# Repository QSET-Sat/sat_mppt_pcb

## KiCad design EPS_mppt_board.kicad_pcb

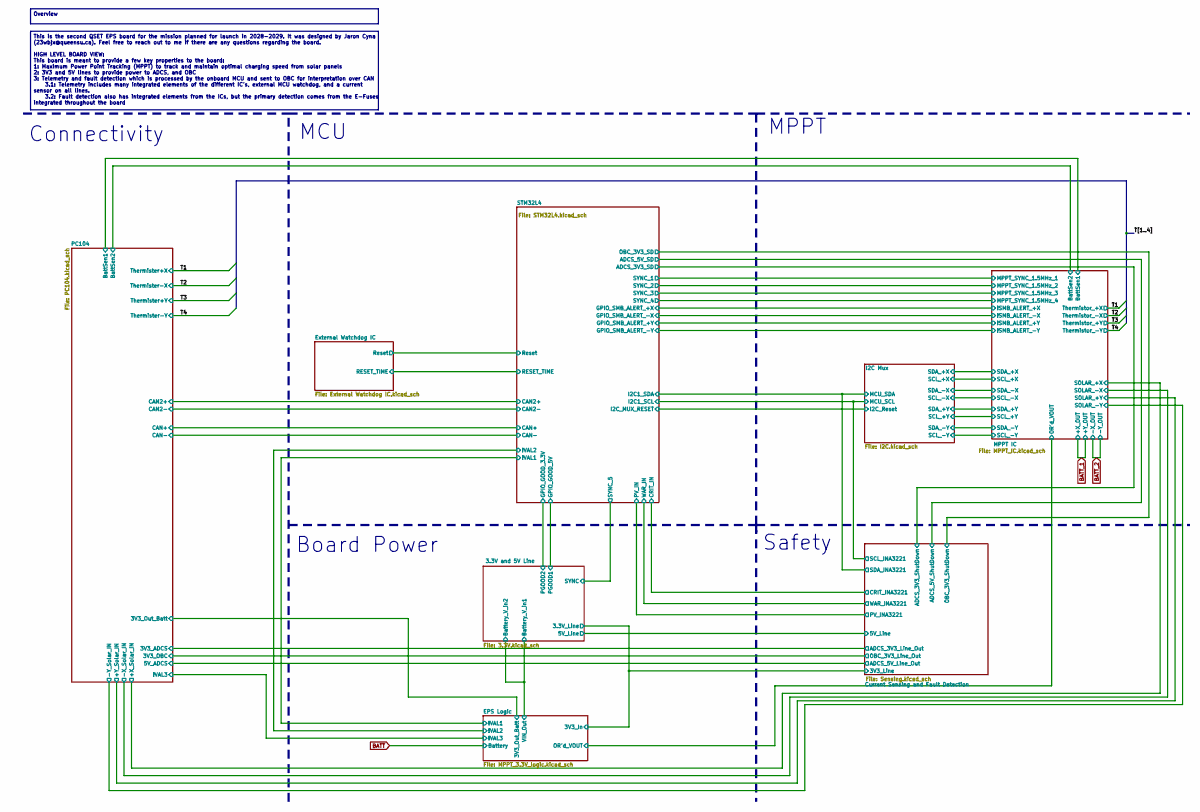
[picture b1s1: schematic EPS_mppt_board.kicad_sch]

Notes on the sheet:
MCU
MPPT
Safety
Board Power
Connectivity
This is the second QSET EPS board for the mission planned for launch in 2028-2029. It was designed by Jaron Cyna (23wbjx@queensu.ca). Feel free to reach out to me if there are any questions regarding the board. HIGH LEVEL BOARD VIEW: This board is meant to provide a few key properties to the board: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
Overview

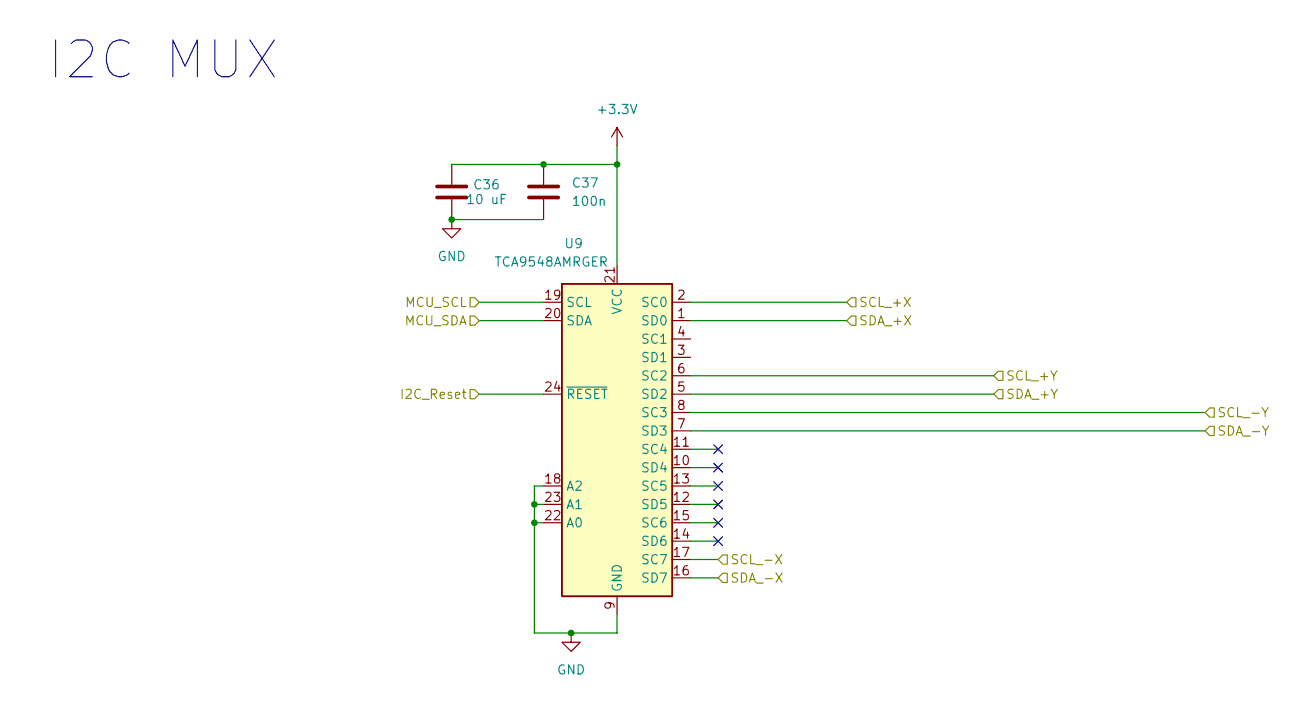
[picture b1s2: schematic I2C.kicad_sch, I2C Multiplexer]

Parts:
C36: 10 uF; C_0603_1608Metric
C37: 100n; C_0603_1608Metric; MANUFACTURER_PART_NUMBER C0603X104K5RACTU
U9: TCA9548AMRGER; Texas_RGE0024C_VQFN-24-1EP_4x4mm_P0.5mm_EP2.1x2.1mm

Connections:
+3.3V: C36.2, C37.1, U9.21 (VCC); also elsewhere on the board
/Current Sensing and Fault Detection/SCL_INA3221: U9.19 (SCL); also elsewhere on the board
/Current Sensing and Fault Detection/SDA_INA3221: U9.20 (SDA); also elsewhere on the board
/I2C Mux/I2C_Reset: U9.24 (~RESET); also elsewhere on the board
/I2C Mux/SCL_+X: U9.2 (SC0); also elsewhere on the board
/I2C Mux/SCL_+Y: U9.6 (SC2); also elsewhere on the board
/I2C Mux/SCL_-X: U9.17 (SC7); also elsewhere on the board
/I2C Mux/SCL_-Y: U9.8 (SC3); also elsewhere on the board
/I2C Mux/SDA_+X: U9.1 (SD0); also elsewhere on the board
/I2C Mux/SDA_+Y: U9.5 (SD2); also elsewhere on the board
/I2C Mux/SDA_-X: U9.16 (SD7); also elsewhere on the board
/I2C Mux/SDA_-Y: U9.7 (SD3); also elsewhere on the board

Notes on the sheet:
I2C MUX

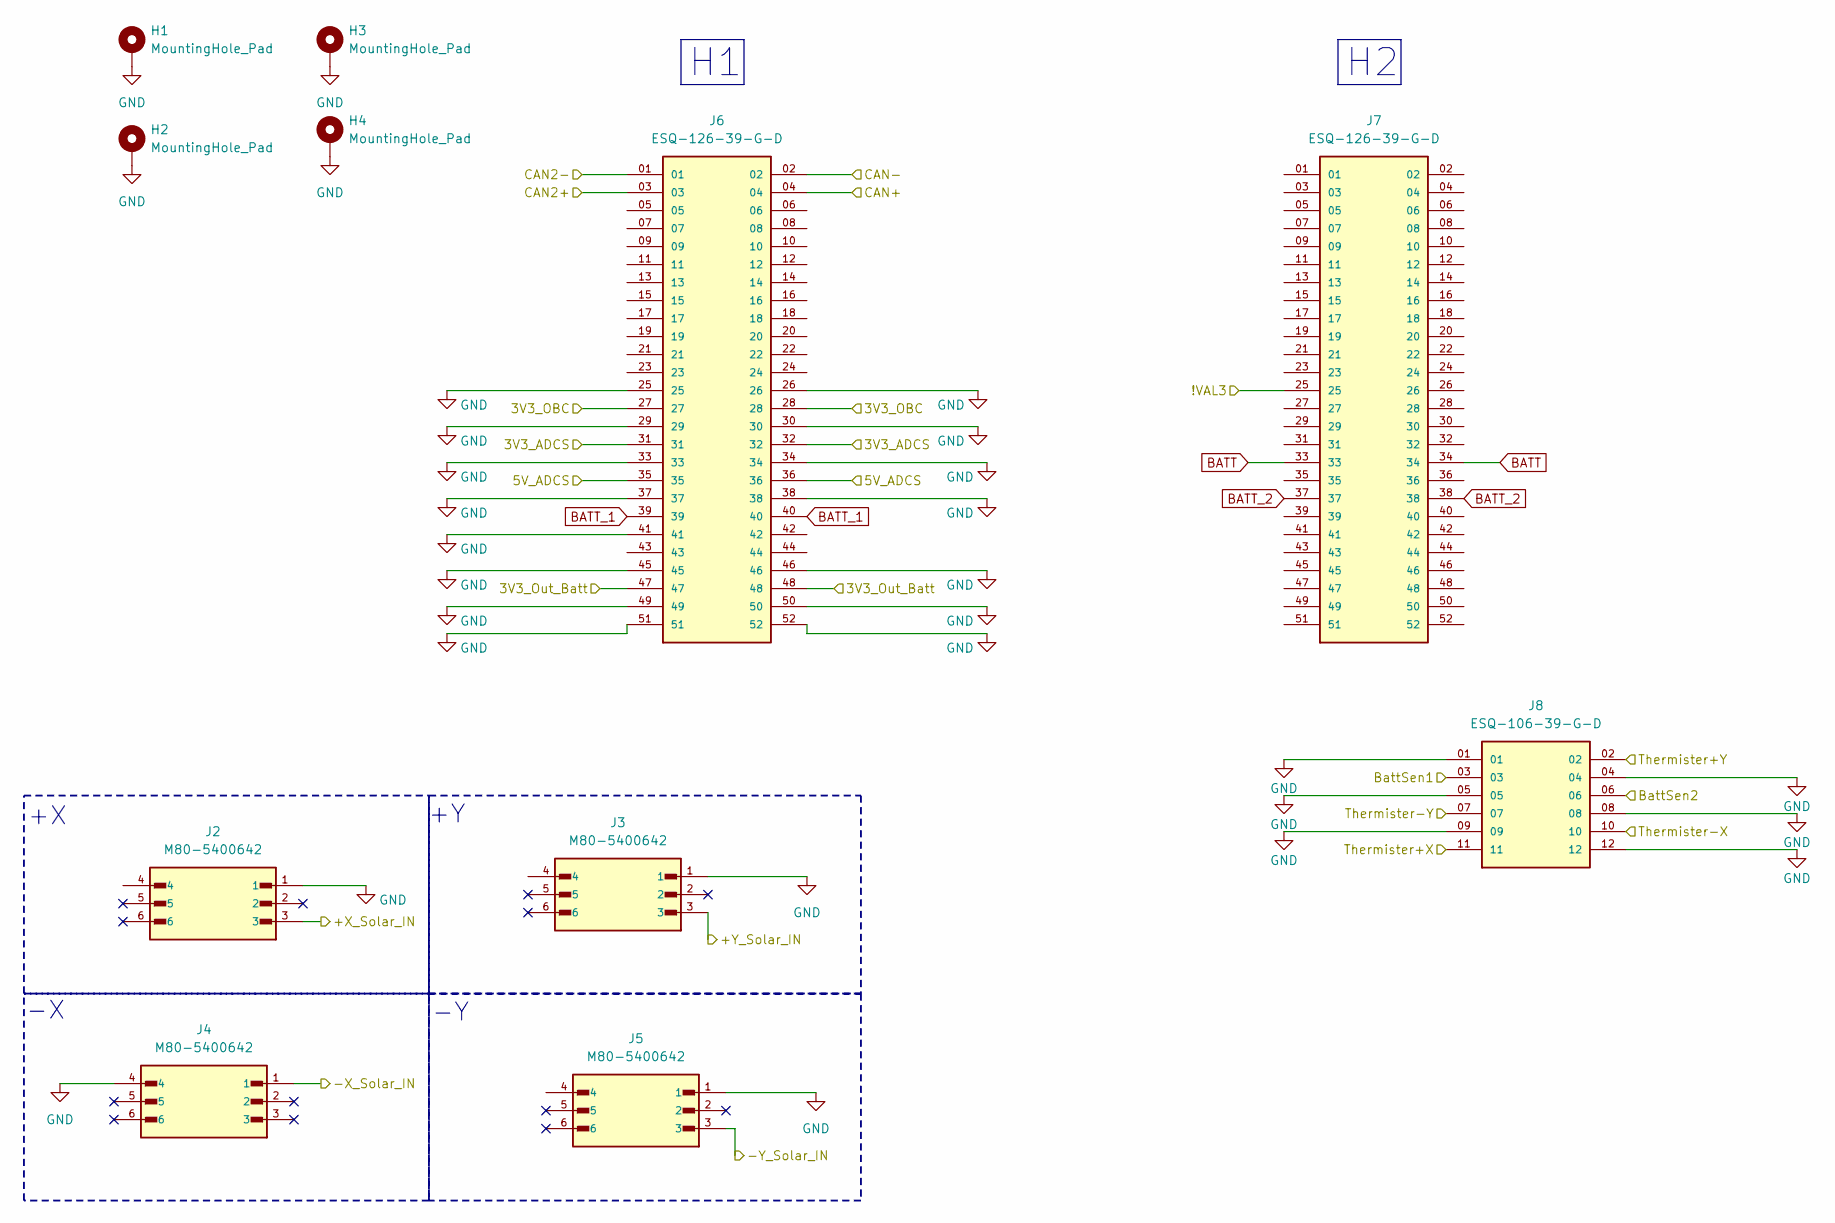
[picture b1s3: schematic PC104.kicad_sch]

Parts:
H1, H2, H3, H4: MountingHole_Pad; MountingHole_3.2mm_M3_Pad
J2, J3, J4, J5: M80-5400642; HARWIN_M80-5400642
J6, J7: ESQ-126-39-G-D; SAMTEC_ESQ-126-39-G-D; PARTREV R
J8: ESQ-106-39-G-D; SAMTEC_ESQ-106-39-G-D; PARTREV R

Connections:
/Current Sensing and Fault Detection/ADCS_3V3_Line_Out: J6.31, J6.32; also elsewhere on the board
/Current Sensing and Fault Detection/ADCS_5V_Line_Out: J6.35, J6.36; also elsewhere on the board
/Current Sensing and Fault Detection/OBC_3V3_Line_Out: J6.27, J6.28; also elsewhere on the board
/EPS Logic/3V3_Out_Batt: J6.47, J6.48; also elsewhere on the board
/EPS Logic/!VAL3: J7.25; also elsewhere on the board
/MPPT IC/BattSen1: J8.03; also elsewhere on the board
/MPPT IC/BattSen2: J8.06; also elsewhere on the board
/MPPT IC/SOLAR_+X: J2.3; also elsewhere on the board
/MPPT IC/SOLAR_+Y: J3.3; also elsewhere on the board
/MPPT IC/SOLAR_-X: J4.1; also elsewhere on the board
/MPPT IC/SOLAR_-Y: J5.3; also elsewhere on the board
/PC104/CAN2+: J6.03; also elsewhere on the board
/PC104/CAN2-: J6.01; also elsewhere on the board
/PC104/CAN+: J6.04; also elsewhere on the board
/PC104/CAN-: J6.02; also elsewhere on the board
/T1: J8.11; also elsewhere on the board
/T2: J8.10; also elsewhere on the board
/T3: J8.02; also elsewhere on the board
/T4: J8.07; also elsewhere on the board
BATT: J7.33, J7.34; also elsewhere on the board
BATT_1: J6.39, J6.40; also elsewhere on the board
BATT_2: J7.37, J7.38; also elsewhere on the board

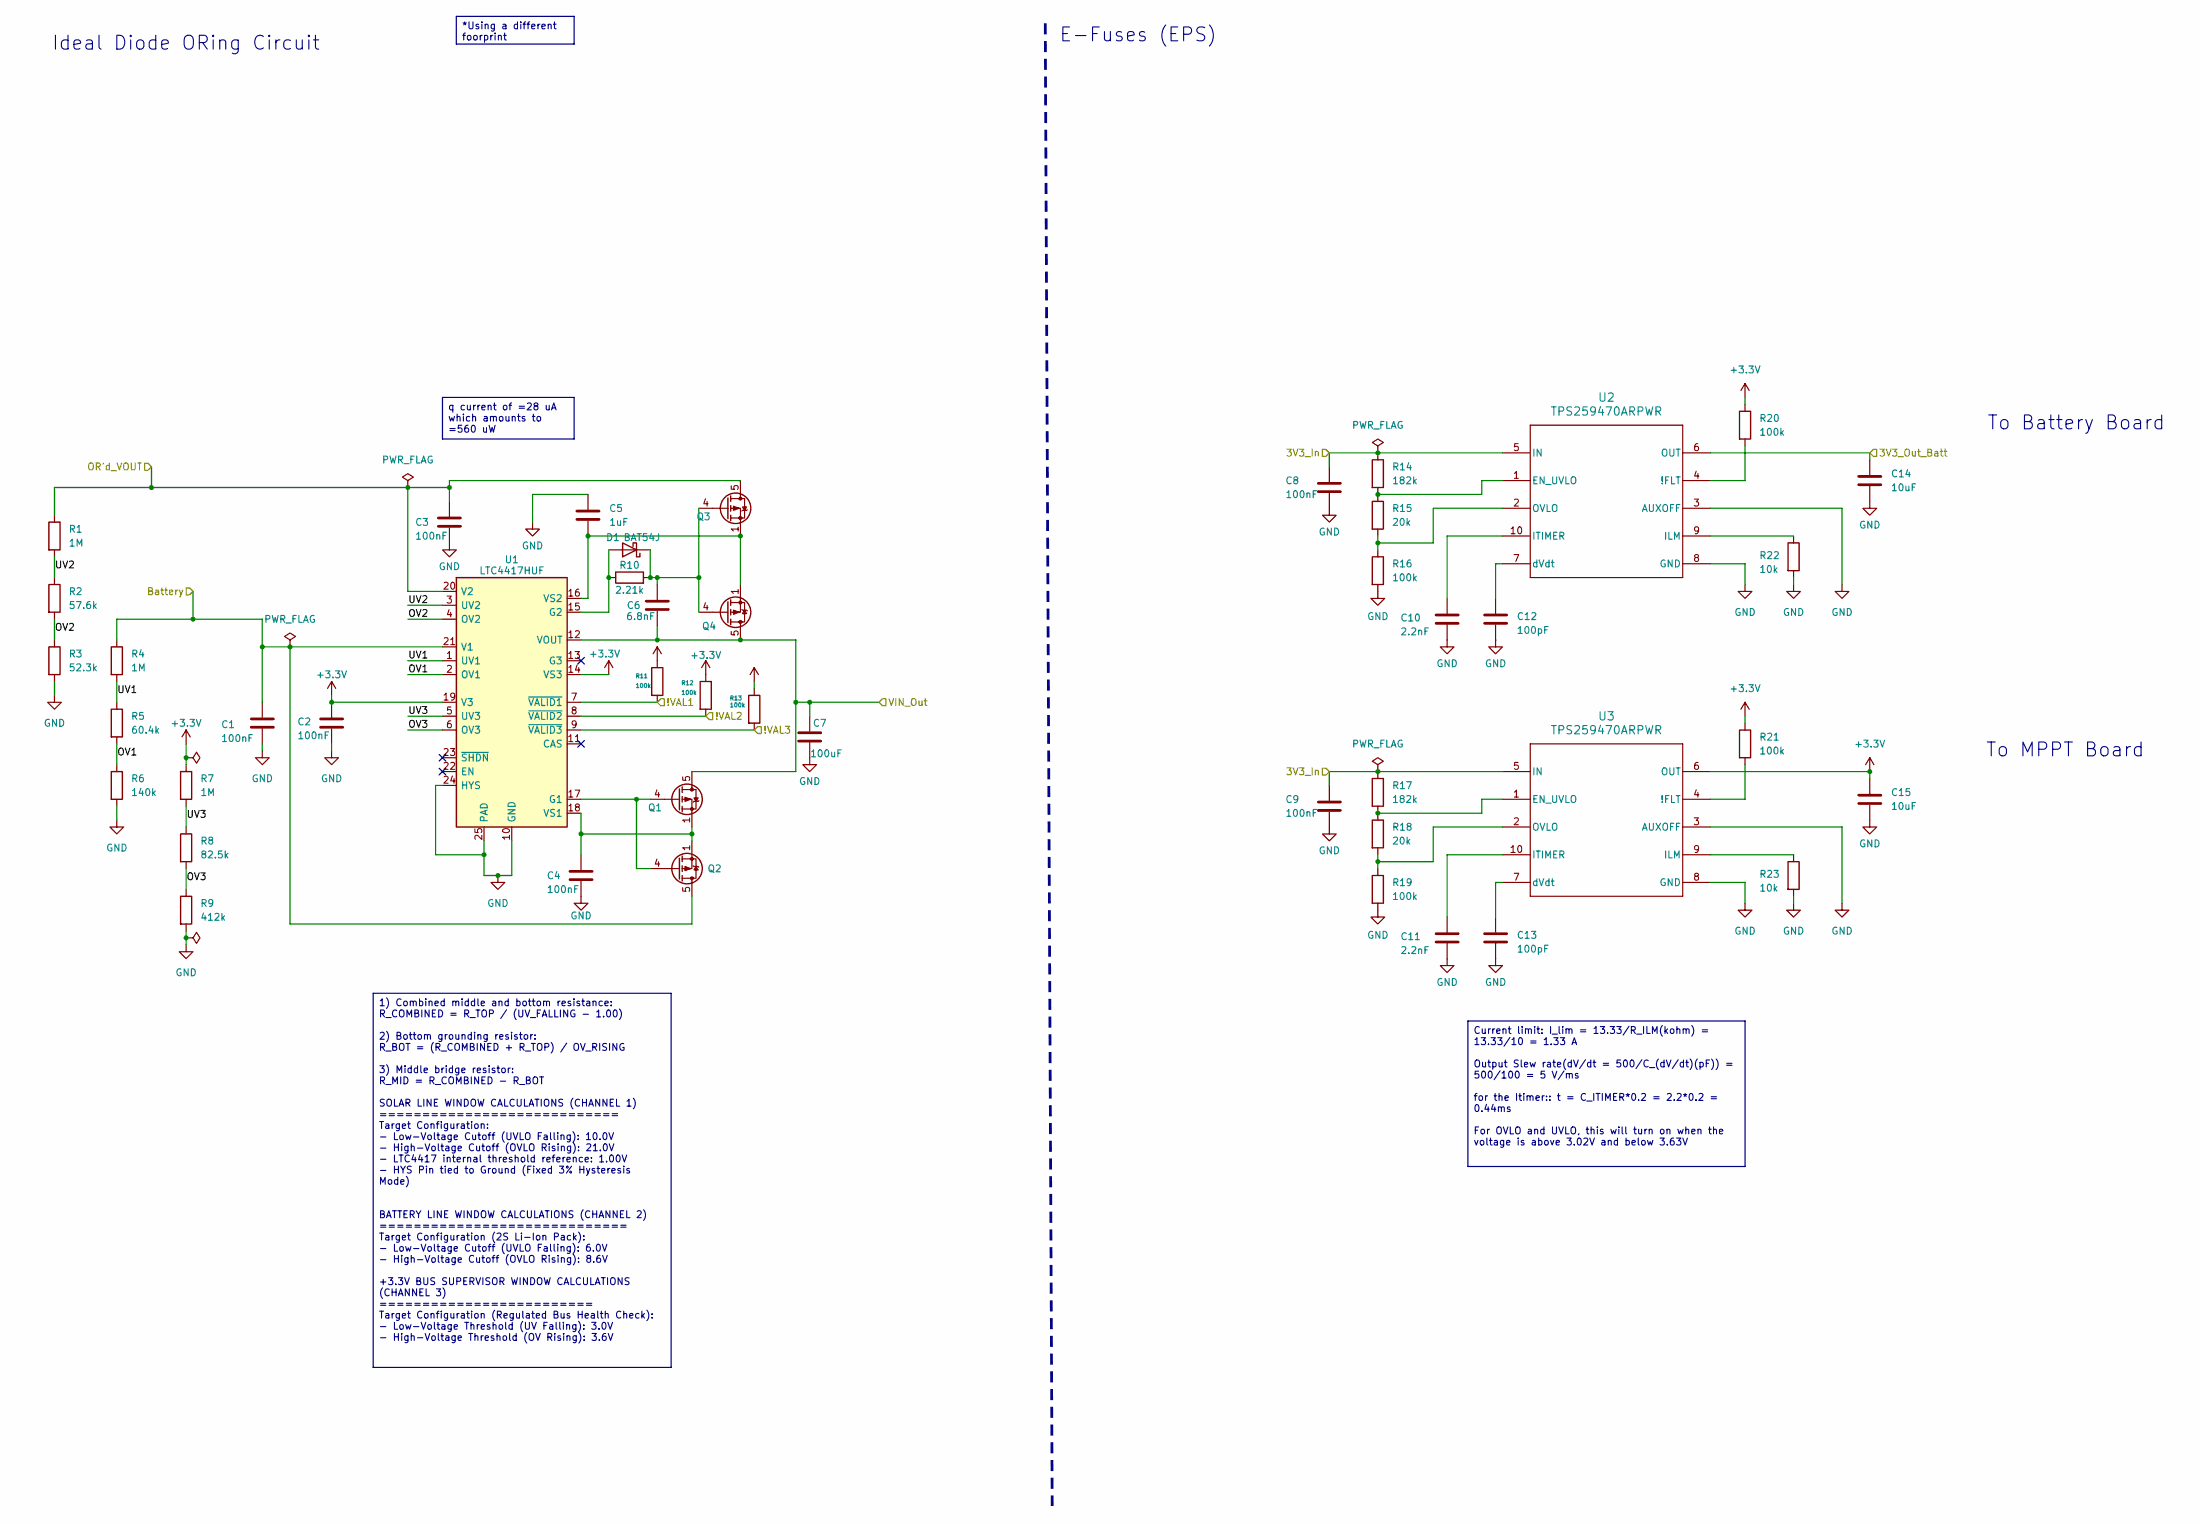
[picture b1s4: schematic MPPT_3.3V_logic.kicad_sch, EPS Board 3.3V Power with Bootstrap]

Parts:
C1, C2, C3, C4, C8, C9: 100nF; C_0603_1608Metric; MANUFACTURER_PART_NUMBER 06035C104K4T2A
C5: 1uF; C_0603_1608Metric; MANUFACTURER_PART_NUMBER CL10B105KQ8NNNC
C6: 6.8nF; C_0603_1608Metric; MANUFACTURER_PART_NUMBER KAM15AR71H682JT
C7: 100uF; CP_EIA-7361-38_AVX-V; MANUFACTURER_PART_NUMBER T52M9107M035C0055
C10, C11: 2.2nF; C_0603_1608Metric; MANUFACTURER_PART_NUMBER GCM1885C1H222FA16D
C12, C13: 100pF; C_0603_1608Metric; MANUFACTURER_PART_NUMBER 885342206001
C14, C15: 10uF; C_1206_3216Metric; MANUFACTURER_PART_NUMBER AVX, 04025C104KAT2A
D1: BAT54J; D_SOD-323F
Q1, Q2, Q3, Q4: SIR5607DP-T1-RE3; PowerPAK_SO-8_Single; MANUFACTURER_PART_NUMBER SIR5607DP-T1-RE3
R1, R4, R7: 1M; R_0603_1608Metric; MANUFACTURER_PART_NUMBER CPF0603B1M0E
R2: 57.6k; R_0603_1608Metric; MANUFACTURER_PART_NUMBER RT0603BRD0757K6L
R3: 52.3k; R_0603_1608Metric; MANUFACTURER_PART_NUMBER ERA-3AEB5232V
R5: 60.4k; R_0603_1608Metric; MANUFACTURER_PART_NUMBER RT0603FRE0760K4L
R6: 140k; R_0603_1608Metric; MANUFACTURER_PART_NUMBER RT0603BRD07140KL
R8: 82.5k; R_0603_1608Metric; MANUFACTURER_PART_NUMBER ERA-3AEB8252V
R9: 412k; R_0603_1608Metric; MANUFACTURER_PART_NUMBER RT0603BRD07412KL
R10: 2.21k; R_0603_1608Metric; MANUFACTURER_PART_NUMBER RMCF0603FT2K21
R11, R12, R13, R16, R19, R20, R21: 100k; R_0603_1608Metric; MANUFACTURER_PART_NUMBER AT0603FRE07100KL
R14, R17: 182k; R_0603_1608Metric
R15, R18: 20k; R_0603_1608Metric
R22, R23: 10k; R_0805_2012Metric; MANUFACTURER_PART_NUMBER TNPW080510K0FEEA
U1: LTC4417HUF; QFN-24-1EP_4x4mm_P0.5mm_EP2.6x2.6mm
U2, U3: TPS259470ARPWR; RPW0010A-MFG

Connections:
+3.3V: C2.1, C15.1, R7.1, R11.1, R12.1, R13.1, R20.1, R21.1, U1.14 (VS3), U1.19 (V3), U3.6 (OUT); also elsewhere on the board
/3.3V and 5V Line/Battery_V_in1: C6.1, C7.1, Q1.5 (D), Q4.5 (D), U1.12 (VOUT); also elsewhere on the board
/EPS Logic/3V3_Out_Batt: C14.1, U2.6 (OUT); also elsewhere on the board
/EPS Logic/!VAL1: R11.2, U1.7 (~VALID1); also elsewhere on the board
/EPS Logic/!VAL2: R12.2, U1.8 (~VALID2); also elsewhere on the board
/EPS Logic/!VAL3: R13.2, U1.9 (~VALID3); also elsewhere on the board
/EPS Logic/OR'd_VOUT: C3.1, Q3.5 (D), R1.1, U1.20 (V2); also elsewhere on the board
/EPS Logic/OV1: R5.2, R6.1, U1.2 (OV1)
/EPS Logic/OV2: R2.2, R3.1, U1.4 (OV2)
/EPS Logic/OV3: R8.2, R9.1, U1.6 (OV3)
/EPS Logic/UV1: R4.2, R5.1, U1.1 (UV1)
/EPS Logic/UV2: R1.2, R2.1, U1.3 (UV2)
/EPS Logic/UV3: R7.2, R8.1, U1.5 (UV3)
BATT: C1.1, Q2.5 (D), R4.1, U1.21 (V1); also elsewhere on the board
unnamed: D1.2 (A), R10.1, U1.15 (G2)
unnamed: C6.2, D1.1 (K), Q3.4 (G), Q4.4 (G), R10.2
unnamed: Q1.4 (G), Q2.4 (G), U1.17 (G1)
unnamed: C4.1, Q1.1 (S), Q1.2 (S), Q1.3 (S), Q2.1 (S), Q2.2 (S), Q2.3 (S), U1.18 (VS1)
unnamed: C5.2, Q3.1 (S), Q3.2 (S), Q3.3 (S), Q4.1 (S), Q4.2 (S), Q4.3 (S), U1.16 (VS2)
unnamed: R20.2, U2.4 (!FLT)
unnamed: R14.2, R15.1, U2.1 (EN_UVLO)
unnamed: R22.1, U2.9 (ILM)
unnamed: C10.1, U2.10 (ITIMER)
unnamed: R15.2, R16.1, U2.2 (OVLO)
unnamed: C12.1, U2.7 (dVdt)
unnamed: R21.2, U3.4 (!FLT)
unnamed: R17.2, R18.1, U3.1 (EN_UVLO)
unnamed: R23.1, U3.9 (ILM)
unnamed: C11.1, U3.10 (ITIMER)
unnamed: R18.2, R19.1, U3.2 (OVLO)
unnamed: C13.1, U3.7 (dVdt)

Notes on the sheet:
To Battery Board
E-Fuses (EPS)
To MPPT Board
Ideal Diode ORing Circuit
q current of =28 uA which amounts to =560 uW
*Using a different foorprint
Current limit: I_lim = 13.33/R_ILM(kohm) = 13.33/10 = 1.33 A Output Slew rate(dV/dt = 500/C_(dV/dt)(pF)) = 500/100 = 5 V/ms for the Itimer:: t = C_ITIMER*0.2 = 2.2*0.2 = 0.44ms For OVLO and UVLO, this will turn on when the voltage is above 3.02V and below 3.63V
1) Combined middle and bottom resistance: R_COMBINED = R_TOP / (UV_FALLING - 1.00) 2) Bottom grounding resistor: R_BOT = (R_COMBINED + R_TOP) / OV_RISING 3) Middle bridge resistor: R_MID = R_COMBINED - R_BOT SOLAR LINE WINDOW CALCULATIONS (CHANNEL 1) ============================ Target Configuratio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

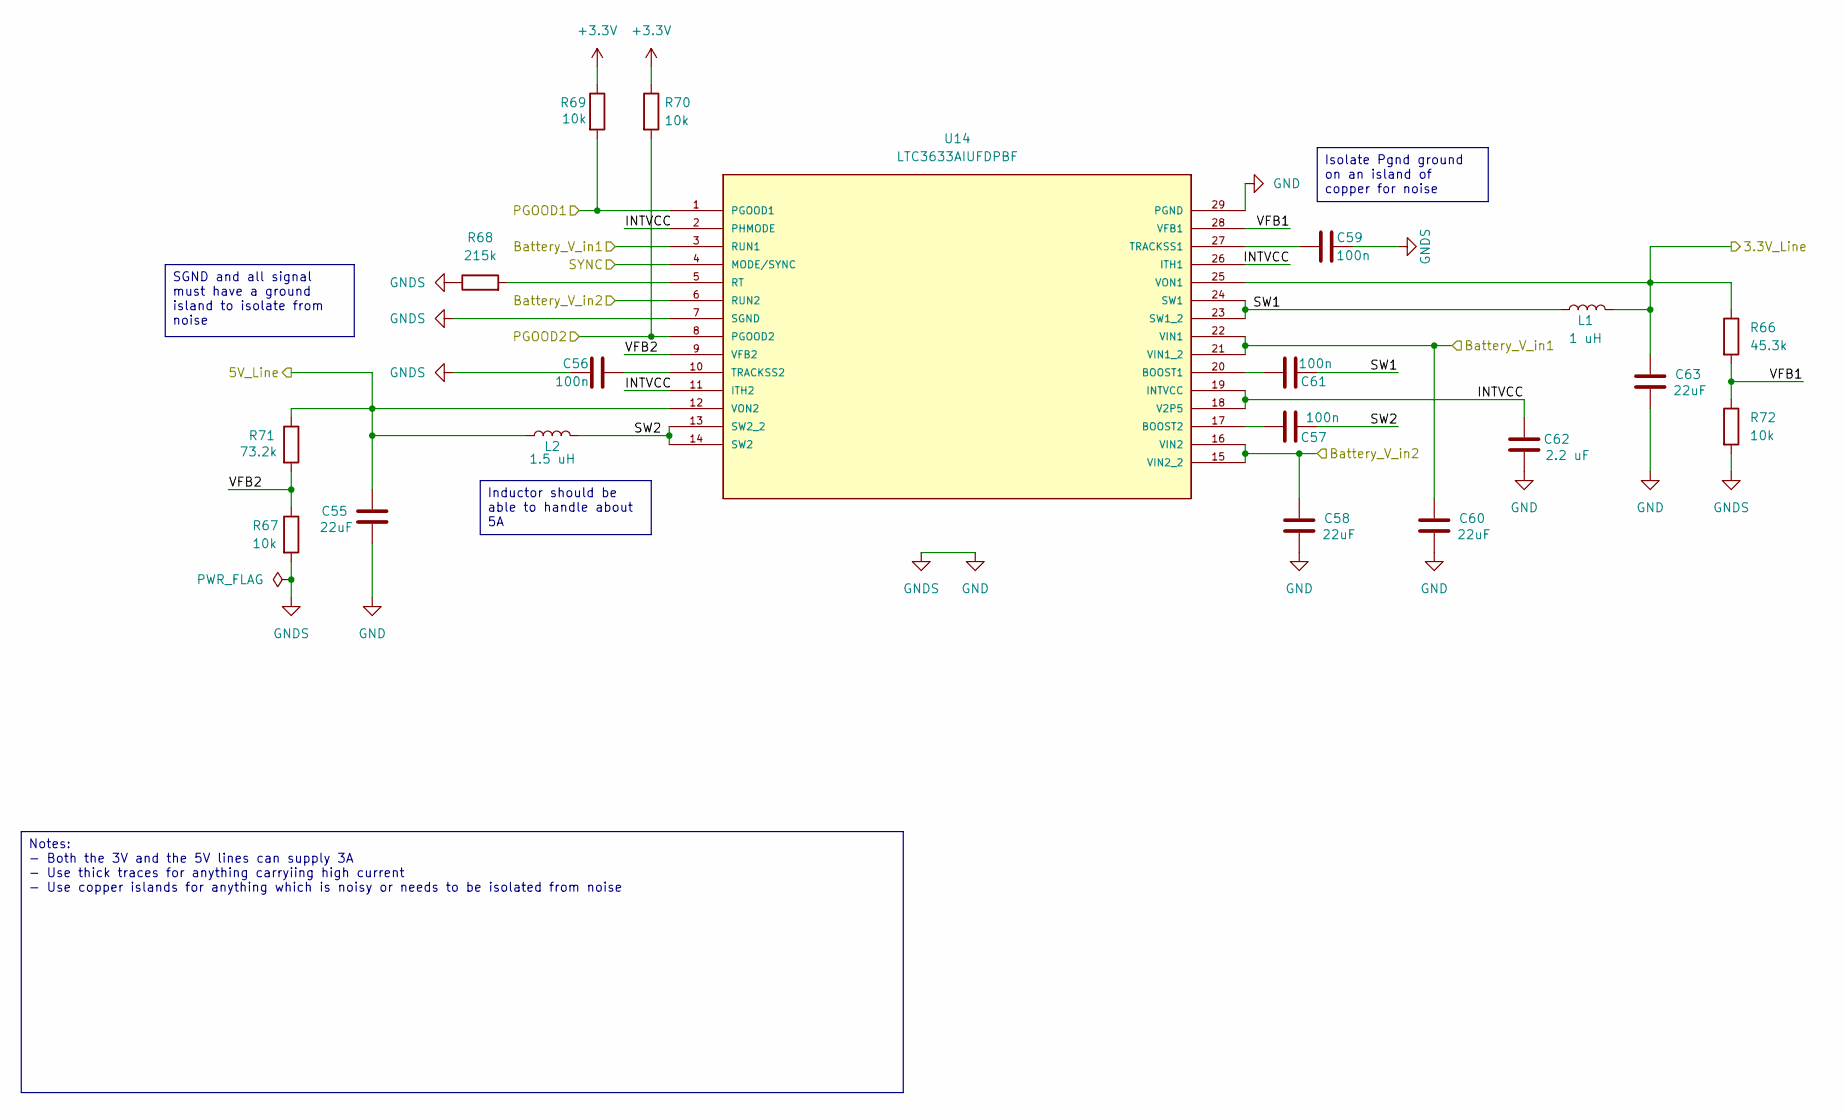
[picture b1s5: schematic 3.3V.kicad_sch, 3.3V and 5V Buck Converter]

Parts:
C55, C58, C60, C63: 22uF; C_1210_3225Metric; MANUFACTURER_PART_NUMBER CGA6P3X7R1E226M250AE
C56, C57, C59, C61: 100n; C_0603_1608Metric; MANUFACTURER_PART_NUMBER 06035C104K4T2A
C62: 2.2 uF; C_0402_1005Metric
L1: 1 uH; IND_PA4332_PUL-M; MANUFACTURER_PART_NUMBER PA4332.102NLT
L2: 1.5 uH; IND_SRP4020_BRN-M; MANUFACTURER_PART_NUMBER SRP4020TA-1R5M
R66: 45.3k; R_0603_1608Metric
R67, R69, R70, R72: 10k; R_0805_2012Metric; MANUFACTURER_PART_NUMBER TNPW080510K0FEEA
R68: 215k; R_0603_1608Metric
R71: 73.2k; R_0603_1608Metric
U14: LTC3633AIUFDPBF; QFN-28-1EP_4x5mm_P0.5mm_EP2.65x3.65mm_ThermalVias; MANUFACTURER_PART_NUMBER ltc3633aiufd#pbf

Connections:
+3.3V: R69.1, R70.1; also elsewhere on the board
/3.3V and 5V Line/Battery_V_in1: C58.1, C60.1, U14.3 (RUN1), U14.6 (RUN2), U14.15 (VIN2_2), U14.16 (VIN2), U14.21 (VIN1_2), U14.22 (VIN1); also elsewhere on the board
/3.3V and 5V Line/PGOOD1: R69.2, U14.1 (PGOOD1); also elsewhere on the board
/3.3V and 5V Line/PGOOD2: R70.2, U14.8 (PGOOD2); also elsewhere on the board
/3.3V and 5V Line/SYNC: U14.4 (MODE/SYNC); also elsewhere on the board
unnamed: C57.1, U14.17 (BOOST2)
unnamed: C59.1, U14.27 (TRACKSS1)
unnamed: C56.1, U14.10 (TRACKSS2)

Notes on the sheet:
SGND and all signal must have a ground island to isolate from noise
Notes: - Both the 3V and the 5V lines can supply 3A - Use thick traces for anything carryiing high current - Use copper islands for anything which is noisy or needs to be isolated from noise
Isolate Pgnd ground on an island of copper for noise
Inductor should be able to handle about 5A

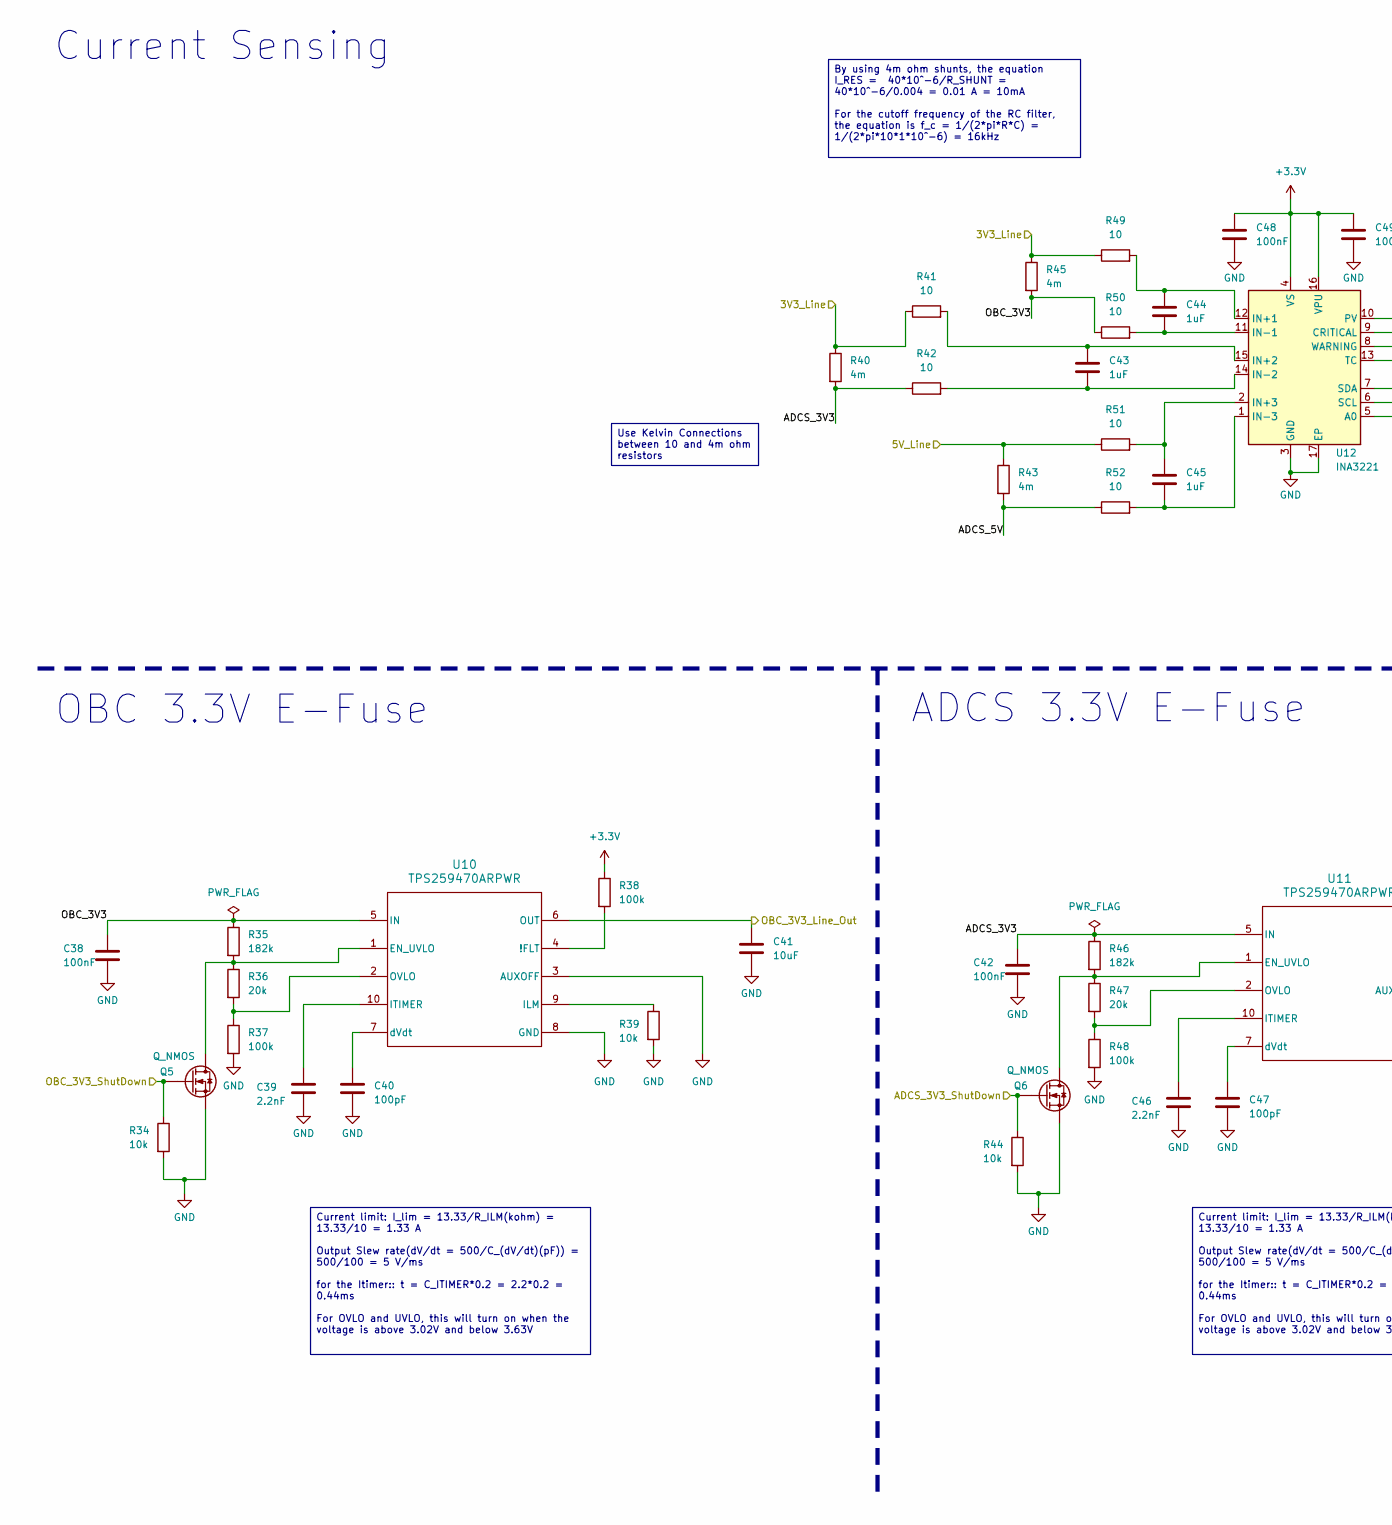
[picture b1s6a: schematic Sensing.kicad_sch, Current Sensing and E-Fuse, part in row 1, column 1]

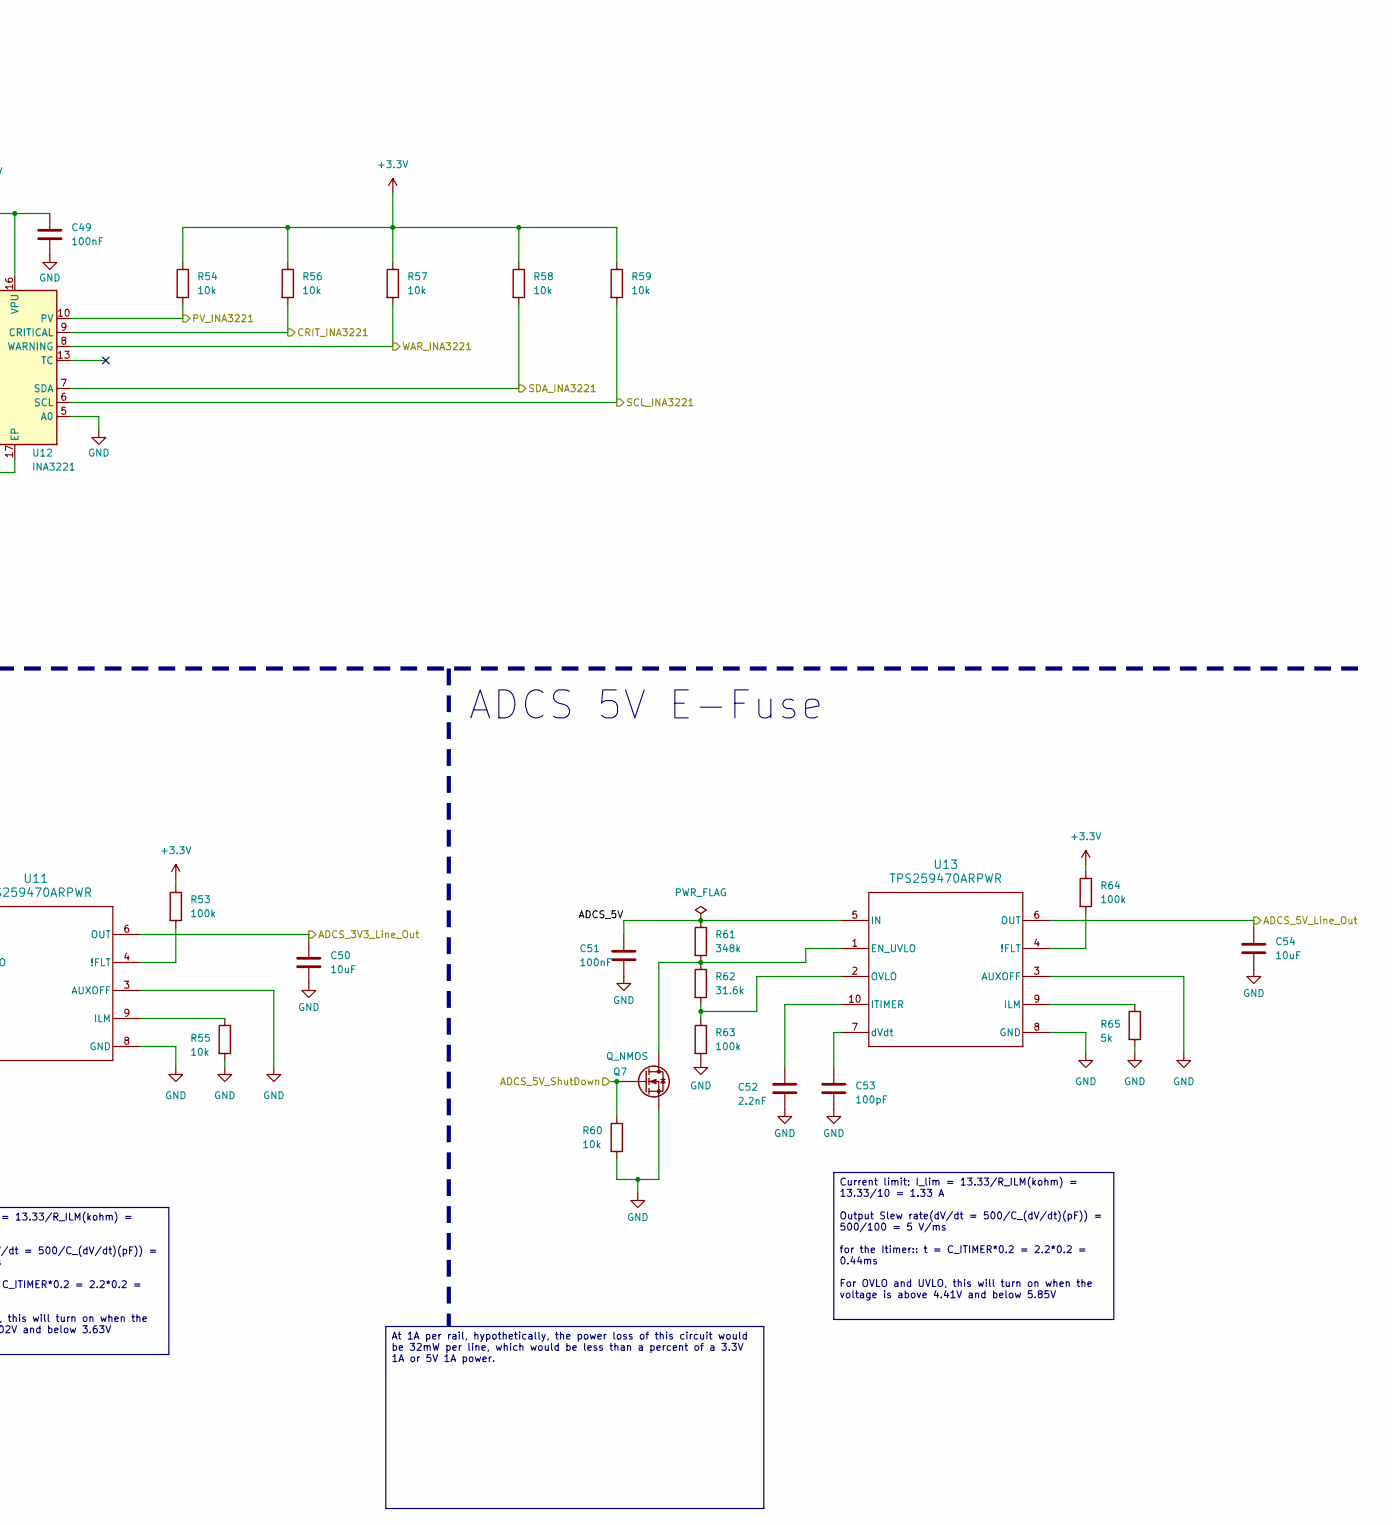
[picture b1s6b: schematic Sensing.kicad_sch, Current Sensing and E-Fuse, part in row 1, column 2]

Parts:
C38, C42, C48, C49, C51: 100nF; C_0603_1608Metric; MANUFACTURER_PART_NUMBER 06035C104K4T2A
C39, C46, C52: 2.2nF; C_0603_1608Metric; MANUFACTURER_PART_NUMBER GCM1885C1H222FA16D
C40, C47, C53: 100pF; C_0603_1608Metric; MANUFACTURER_PART_NUMBER 885342206001
C41, C50, C54: 10uF; C_1206_3216Metric; MANUFACTURER_PART_NUMBER AVX, 04025C104KAT2A
C43, C44, C45: 1uF; C_0603_1608Metric; MANUFACTURER_PART_NUMBER CL10B105KQ8NNNC
Q5, Q6, Q7: Q_NMOS; IFX-PG-TSDSON-8-44-V; MANUFACTURER_PART_NUMBER IAUZN04S7L046ATMA1
R34, R39, R44, R54, R55, R56, R57, R58, R59, R60: 10k; R_0805_2012Metric; MANUFACTURER_PART_NUMBER TNPW080510K0FEEA
R35, R46: 182k; R_0603_1608Metric
R36, R47: 20k; R_0603_1608Metric
R37, R38, R48, R53, R63, R64: 100k; R_0603_1608Metric; MANUFACTURER_PART_NUMBER AT0603FRE07100KL
R40, R43, R45: 4m; R_0815_2038Metric; MANUFACTURER_PART_NUMBER RL3720WT-R004-F
R41, R42, R49, R50, R51, R52: 10; R_0805_2012Metric; MANUFACTURER_PART_NUMBER TNPW080510R0BEEA
R61: 348k; R_0603_1608Metric
R62: 31.6k; R_0603_1608Metric
R65: 5k; R_0603_1608Metric; MANUFACTURER_PART_NUMBER RN73R1JTTD4991F100
U10, U11, U13: TPS259470ARPWR; RPW0010A-MFG
U12: INA3221; Texas_RGV0016A_VQFN-16-1EP_4x4mm_P0.65mm_EP2.1x2.1mm

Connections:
+3.3V: C48.1, C49.1, R38.1, R53.1, R54.1, R56.1, R57.1, R58.1, R59.1, R64.1, U12.4 (VS), U12.16 (VPU); also elsewhere on the board
/Current Sensing and Fault Detection/ADCS_3V3: C42.1, R40.2, R42.1, R46.1, U11.5 (IN)
/Current Sensing and Fault Detection/ADCS_3V3_Line_Out: C50.1, U11.6 (OUT); also elsewhere on the board
/Current Sensing and Fault Detection/ADCS_3V3_ShutDown: Q6.4 (G), R44.1; also elsewhere on the board
/Current Sensing and Fault Detection/ADCS_5V: C51.1, R43.2, R52.1, R61.1, U13.5 (IN)
/Current Sensing and Fault Detection/ADCS_5V_Line_Out: C54.1, U13.6 (OUT); also elsewhere on the board
/Current Sensing and Fault Detection/ADCS_5V_ShutDown: Q7.4 (G), R60.1; also elsewhere on the board
/Current Sensing and Fault Detection/CRIT_INA3221: R56.2, U12.9 (CRITICAL); also elsewhere on the board
/Current Sensing and Fault Detection/OBC_3V3: C38.1, R35.1, R45.2, R50.1, U10.5 (IN)
/Current Sensing and Fault Detection/OBC_3V3_Line_Out: C41.1, U10.6 (OUT); also elsewhere on the board
/Current Sensing and Fault Detection/OBC_3V3_ShutDown: Q5.4 (G), R34.1; also elsewhere on the board
/Current Sensing and Fault Detection/PV_INA3221: R54.2, U12.10 (PV); also elsewhere on the board
/Current Sensing and Fault Detection/SCL_INA3221: R59.2, U12.6 (SCL); also elsewhere on the board
/Current Sensing and Fault Detection/SDA_INA3221: R58.2, U12.7 (SDA); also elsewhere on the board
/Current Sensing and Fault Detection/WAR_INA3221: R57.2, U12.8 (WARNING); also elsewhere on the board
unnamed: R38.2, U10.4 (!FLT)
unnamed: Q5.5 (D), Q5.6 (D), Q5.7 (D), Q5.8 (D), R35.2, R36.1, U10.1 (EN_UVLO)
unnamed: R39.1, U10.9 (ILM)
unnamed: C39.1, U10.10 (ITIMER)
unnamed: R36.2, R37.1, U10.2 (OVLO)
unnamed: C40.1, U10.7 (dVdt)
unnamed: R53.2, U11.4 (!FLT)
unnamed: Q6.5 (D), Q6.6 (D), Q6.7 (D), Q6.8 (D), R46.2, R47.1, U11.1 (EN_UVLO)
unnamed: R55.1, U11.9 (ILM)
unnamed: C46.1, U11.10 (ITIMER)
unnamed: R47.2, R48.1, U11.2 (OVLO)
unnamed: C47.1, U11.7 (dVdt)
unnamed: C44.1, R49.2, U12.12 (IN+1)
unnamed: C43.1, R41.2, U12.15 (IN+2)
unnamed: C45.1, R51.2, U12.2 (IN+3)
unnamed: C44.2, R50.2, U12.11 (IN-1)
unnamed: C43.2, R42.2, U12.14 (IN-2)
unnamed: C45.2, R52.2, U12.1 (IN-3)
unnamed: R64.2, U13.4 (!FLT)
unnamed: Q7.5 (D), Q7.6 (D), Q7.7 (D), Q7.8 (D), R61.2, R62.1, U13.1 (EN_UVLO)
unnamed: R65.1, U13.9 (ILM)
unnamed: C52.1, U13.10 (ITIMER)
unnamed: R62.2, R63.1, U13.2 (OVLO)
unnamed: C53.1, U13.7 (dVdt)

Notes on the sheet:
Current Sensing
OBC 3.3V E-Fuse
ADCS 5V E-Fuse
ADCS 3.3V E-Fuse
Current limit: I_lim = 13.33/R_ILM(kohm) = 13.33/10 = 1.33 A Output Slew rate(dV/dt = 500/C_(dV/dt)(pF)) = 500/100 = 5 V/ms for the Itimer:: t = C_ITIMER*0.2 = 2.2*0.2 = 0.44ms For OVLO and UVLO, this will turn on when the voltage is above 3.02V and below 3.63V
By using 4m ohm shunts, the equation I_RES = 40*10^-6/R_SHUNT = 40*10^-6/0.004 = 0.01 A = 10mA For the cutoff frequency of the RC filter, the equation is f_c = 1/(2*pi*R*C) = 1/(2*pi*10*1*10^-6) = 16kHz
Current limit: I_lim = 13.33/R_ILM(kohm) = 13.33/10 = 1.33 A Output Slew rate(dV/dt = 500/C_(dV/dt)(pF)) = 500/100 = 5 V/ms for the Itimer:: t = C_ITIMER*0.2 = 2.2*0.2 = 0.44ms For OVLO and UVLO, this will turn on when the voltage is above 4.41V and below 5.85V
Use Kelvin Connections between 10 and 4m ohm resistors
At 1A per rail, hypothetically, the power loss of this circuit would be 32mW per line, which would be less than a percent of a 3.3V 1A or 5V 1A power.

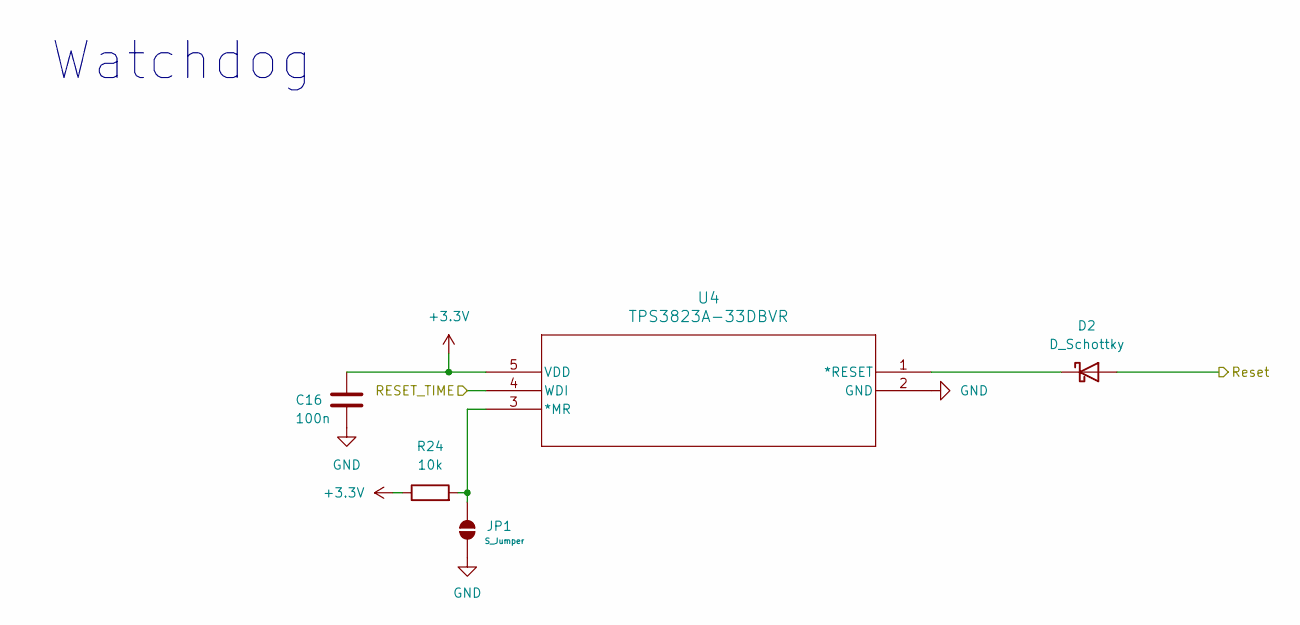
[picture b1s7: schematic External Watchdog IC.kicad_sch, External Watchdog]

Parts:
C16: 100n; C_0603_1608Metric; MANUFACTURER_PART_NUMBER C0603X104K5RACTU
D2: D_Schottky; D_0603_1608Metric
JP1: S_Jumper; SolderJumper-2_P1.3mm_Open_TrianglePad1.0x1.5mm
R24: 10k; R_0805_2012Metric; MANUFACTURER_PART_NUMBER TNPW080510K0FEEA
U4: TPS3823A-33DBVR; SOT-23-5_HandSoldering

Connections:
+3.3V: C16.1, R24.1, U4.5 (VDD); also elsewhere on the board
/External Watchdog IC/RESET_TIME: U4.4 (WDI); also elsewhere on the board
/External Watchdog IC/Reset: D2.2 (A); also elsewhere on the board
unnamed: D2.1 (K), U4.1 (*RESET)
unnamed: JP1.2 (B), R24.2, U4.3 (*MR)

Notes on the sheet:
Watchdog
